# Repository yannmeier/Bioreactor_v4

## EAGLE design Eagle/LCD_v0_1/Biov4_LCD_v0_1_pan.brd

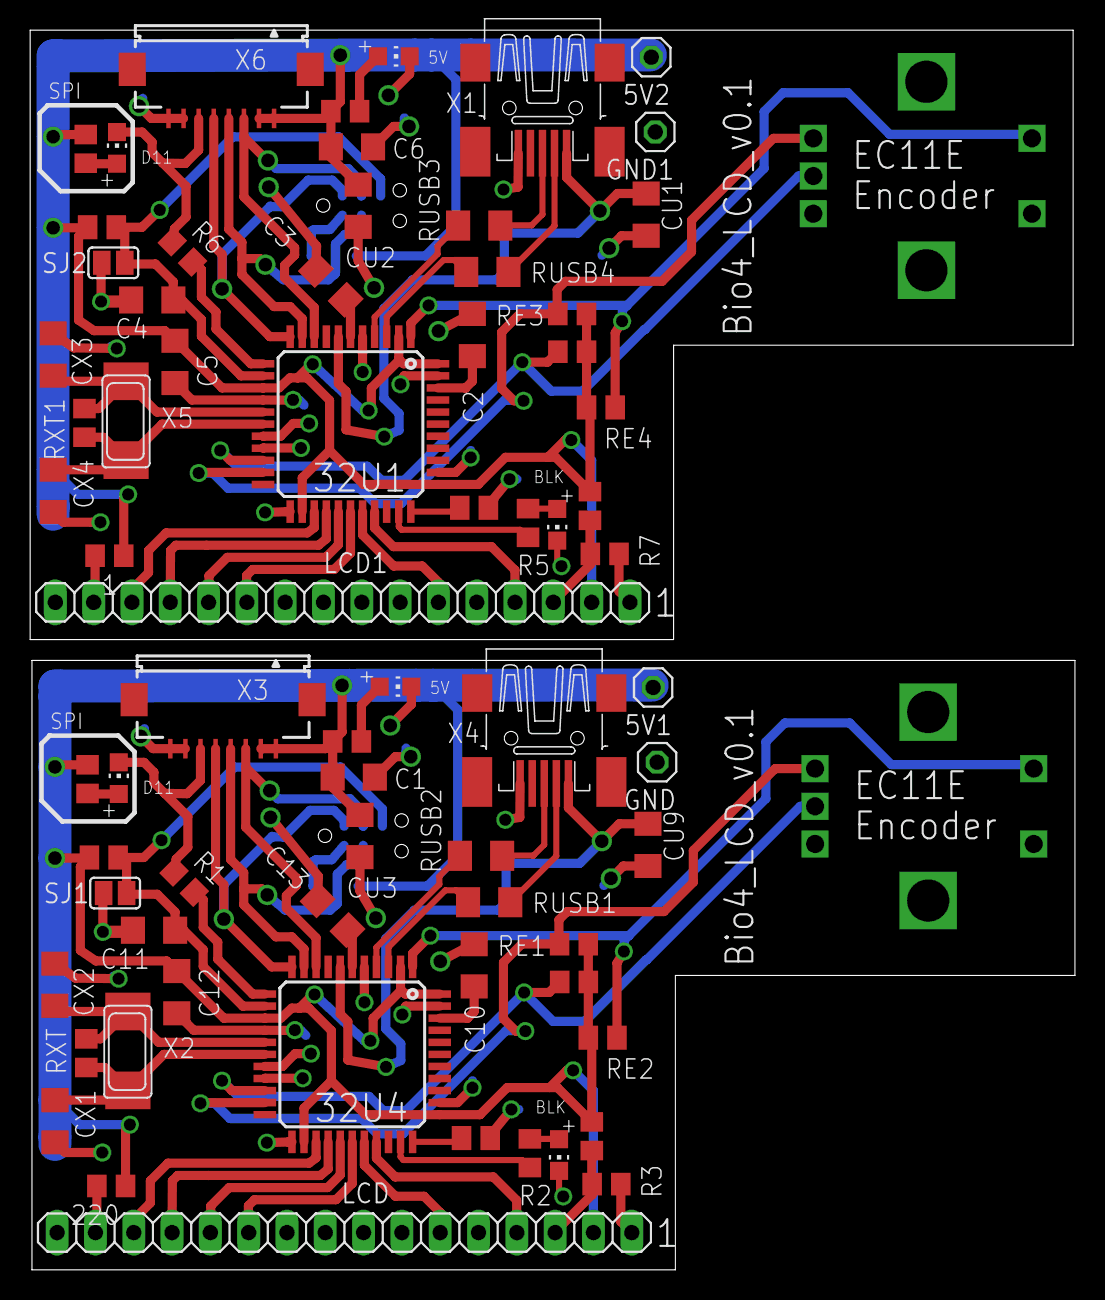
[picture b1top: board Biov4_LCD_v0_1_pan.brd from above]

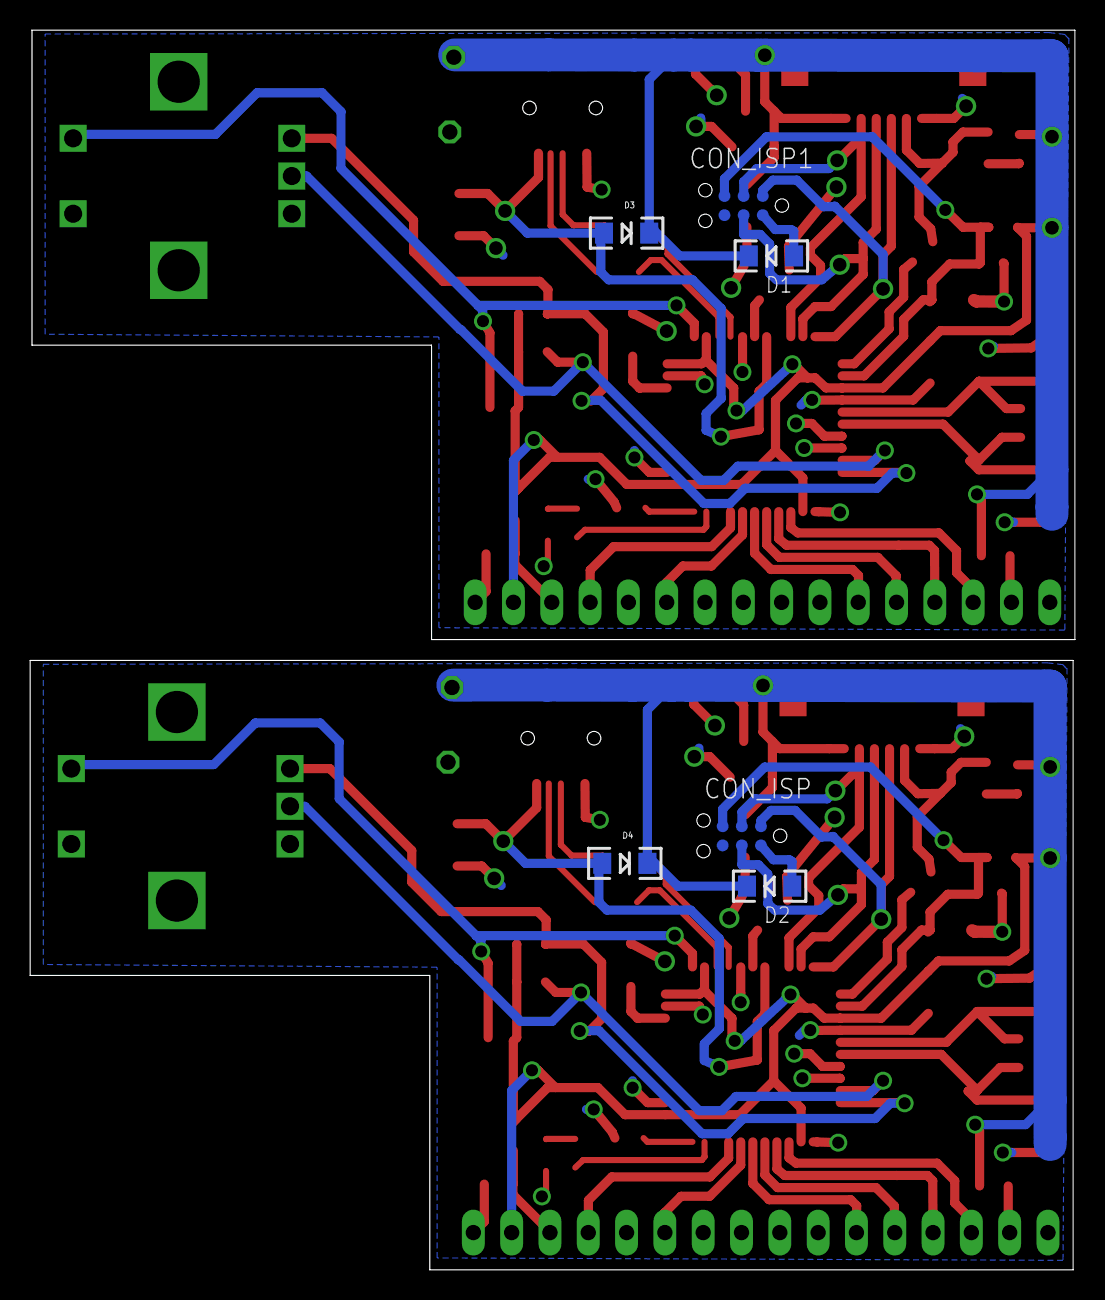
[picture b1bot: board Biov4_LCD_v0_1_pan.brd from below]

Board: 4 copper layers, 69.3 x 82.2 mm, 78 parts (6 on the bottom side), 68 nets.

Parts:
1, 220: 220; R0805
5V1, 5V2: 1X01
32U1, 32U4: ATMEGA32U4; TQFP44
BKLD, BKLD1: RED; CHIP-LED0805
C1, C2, C3, C4, C5, C6, C10, C11, C12, C13: 100nF; C1206
CON_ISP, CON_ISP1: SPI; TC2030-MCP-NL
CU1, CU2, CU3, CU9: 10uF; C1206
CX1, CX2, CX3, CX4: 22pF; C1206
D1, D2, D3, D4: 1N581D1206; LED-1206
GND, GND1: 1X01
LCD, LCD1: 1X16
LDPW1, LDPW5: RED; CHIP-LED0805
LDSLAVE, LDSLAVE1: RED; CHIP-LED0805
R1, R2, R3, R4, R5, R6, R7, R13: 1k; R0805
RE1, RE2, RE3, RE4: 5k; R0805
RK1, RK5, RK8, RK18: 10k; R0805
RK2, RK3, RK4, RK6, RK7, RK9: 10k; M0805
RUSB1, RUSB2, RUSB3, RUSB4: 22; M1206
RXT, RXT1: 1M; R0805
SJ1, SJ2: SJ
U$1, U$2: EC11E
X1, X4: MINI-USB; 32005-201
X2, X5: 16MHz; NX6035
X3, X6: FH12-08S-1SH

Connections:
+5V/1: 5V1.1, 32U4.2, 32U4.14, 32U4.24, 32U4.34, 32U4.44, 220.1, C1.1, C12.2, CU3.1, D2.C, D4.C, LCD.2, R13.1, RE1.1, RE2.1, RK1.1, RK2.2, RK6.2, RK18.1, X3.1, X3.2
+5V/2: 1.1, 5V2.1, 32U1.2, 32U1.14, 32U1.24, 32U1.34, 32U1.44, C5.2, C6.1, CU2.1, D1.C, D3.C, LCD1.2, R4.1, RE3.1, RE4.1, RK4.2, RK5.1, RK8.1, RK9.2, X6.1, X6.2
A6: 32U4.25, LCD.14
A13: 32U1.25, LCD1.14
AREF: 32U4.42, C10.1
AREF1: 32U1.42, C2.1
CS_32U1: LDSLAVE1.C, R6.1, X6.6
CS_32U4: LDSLAVE.C, R1.1, X3.6
D6*: 32U4.27, LCD.12
D6*1: 32U1.27, LCD1.12
D7*: 32U4.1, RK2.1, U$1.D
D7*1: 32U1.1, RK9.1, U$2.D
D8*: 32U4.28, LCD.11
D8*1: 32U1.28, LCD1.11
D9*: 32U4.29, LCD.6
D9*1: 32U1.29, LCD1.6
D10*: 32U4.30, LCD.4
D10*1: 32U1.30, LCD1.4
D11*: 32U4.12, R1.2
D11*1: 32U1.12, R6.2
D12*: 32U4.26, LCD.13
D12*1: 32U1.26, LCD1.13
D13*: 32U4.32, R2.1
D13*1: 32U1.32, R5.1
GND: 32U4.5, 32U4.15, 32U4.23, 32U4.35, 32U4.43, BKLD.C, C1.2, C10.2, C11.2, C12.1, C13.1, CON_ISP.GND, CU3.2, CU9.1, CX1.1, CX2.1, GND.1, LCD.1, LCD.5, LCD.16, LDPW5.C, R3.2, RK7.1, SJ1.1, U$1.C, U$1.E, X3.7, X3.8, X4.5
GND1: 32U1.5, 32U1.15, 32U1.23, 32U1.35, 32U1.43, BKLD1.C, C2.2, C3.1, C4.2, C5.1, C6.2, CON_ISP1.GND, CU1.1, CU2.2, CX3.1, CX4.1, GND1.1, LCD1.1, LCD1.5, LCD1.16, LDPW1.C, R7.2, RK3.1, SJ2.1, U$2.C, U$2.E, X1.5, X6.7, X6.8
HWB: 32U4.33, RK7.2
HWB1: 32U1.33, RK3.2
ISP+5V: CON_ISP.5V, D2.A
ISP+5V1: CON_ISP1.5V, D1.A
MISO: 32U4.11, CON_ISP.MISO, X3.5
MISO1: 32U1.11, CON_ISP1.MISO, X6.5
MOSI: 32U4.10, CON_ISP.MOSI, X3.4
MOSI1: 32U1.10, CON_ISP1.MOSI, X6.4
unnamed: 32U4.6, C13.2
unnamed: LCD.3, R3.1, RK1.2
unnamed: BKLD.A, R2.2
unnamed: LDPW1.A, R4.2
unnamed: BKLD1.A, R5.2
unnamed: 32U1.17, CX4.2, RXT1.2, X5.P$2
unnamed: 32U1.6, C3.2
unnamed: LDSLAVE1.A, RK5.2
unnamed: LCD1.3, R7.1, RK8.2
unnamed: 1.2, LCD1.15
unnamed: 220.2, LCD.15
unnamed: LDPW5.A, R13.2
unnamed: LDSLAVE.A, RK18.2
unnamed: 32U4.17, CX1.2, RXT.2, X2.P$2
RESET: 32U4.13, C11.1, CON_ISP.RESET, RK6.1, SJ1.2
RESET1: 32U1.13, C4.1, CON_ISP1.RESET, RK4.1, SJ2.2
RX: 32U4.20, RE2.2, U$1.B
RX1: 32U1.20, RE4.2, U$2.B
SCK: 32U4.9, CON_ISP.SCK, X3.3
SCK1: 32U1.9, CON_ISP1.SCK, X6.3
TX: 32U4.21, RE1.2, U$1.A
TX1: 32U1.21, RE3.2, U$2.A
USBC_N: RUSB1.2, X4.2
USBC_N1: RUSB4.2, X1.2
USBC_P: RUSB2.2, X4.3
USBC_P1: RUSB3.2, X1.3
USB_N: 32U4.3, RUSB1.1
USB_N1: 32U1.3, RUSB4.1
USB_P: 32U4.4, RUSB2.1
USB_P1: 32U1.4, RUSB3.1
VUSB: 32U4.7, CU9.2, D4.A, X4.1
VUSB1: 32U1.7, CU1.2, D3.A, X1.1
XTAL1: 32U4.16, CX2.2, RXT.1, X2.P$1
XTAL2: 32U1.16, CX3.2, RXT1.1, X5.P$1

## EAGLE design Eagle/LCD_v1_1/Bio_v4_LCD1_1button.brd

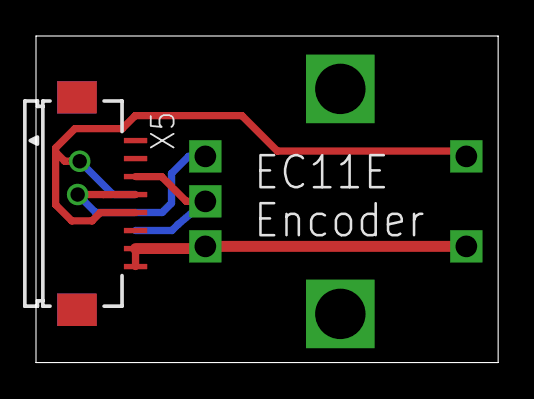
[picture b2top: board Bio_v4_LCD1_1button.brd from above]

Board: 4 copper layers, 25.7 x 18.1 mm, 3 parts (1 on the bottom side), 4 nets.

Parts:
U$1: EC11E
X5, X6: FH12-08S-1SH

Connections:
D7*: U$1.D, X5.5, X6.5
GND: U$1.C, U$1.E, X5.7, X5.8, X6.7, X6.8
RX: U$1.B, X5.3, X6.3
TX: U$1.A, X5.4, X6.4

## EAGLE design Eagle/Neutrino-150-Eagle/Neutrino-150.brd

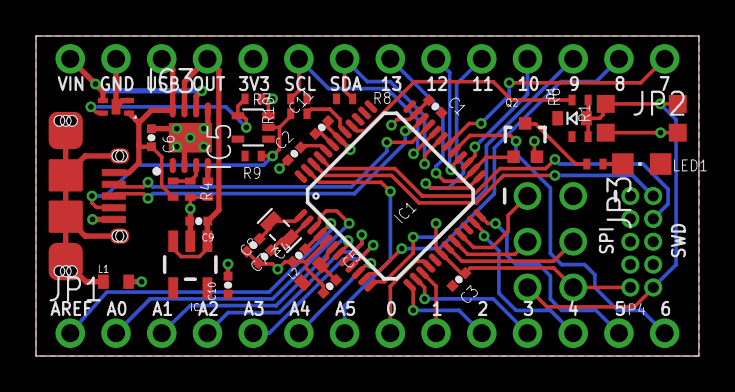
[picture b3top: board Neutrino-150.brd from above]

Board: 2 copper layers, 36.8 x 17.8 mm, 64 parts (0 on the bottom side), 49 nets.

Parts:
C1, C2, C3, C4, C5, C6: 100nF; 0402-CAP
C7, C8: 22pF; 0402-CAP
C9, C10, C11: 1uF; 0402-CAP
D1: SOD-523
IC1: SAMD21G18A-AUT; INTEGRATEDCIRCUITS_TQFP48-7X7
IC2: AP2112K-3.3; SOT23-5
IC3: TPS2115; 8-VDFN
IC4: SIP32401A; TDFN4
IC5: MC74VHC1G14DFT; SC70-5
JP1, JP2: 1X14_NO_SILK_SMALLPADS
JP3: SPI; CONNETTORI_2X03
JP4: SWD; CONNETTORI_PINHEAD-2X5-P127
L1, L2: 0603-TDK
LED1: Green; CHIPLED_0805
Q2: NFET; SOT323
R1, R3, R4, R9, R11: 100K; R0402-VISHAY
R2: 1K; R0402-VISHAY
R5, R6, R10: 330; R0402-VISHAY
R7, R8: 4.7K; R0402-VISHAY
SW1: KMR2
TP_0, TP_1, TP_2, TP_3, TP_3V3, TP_4, TP_5, TP_5V, TP_6, TP_7, TP_8, TP_9, TP_10, TP_12, TP_13: TP_SP; TP-SP
TP_A0, TP_A1, TP_A2, TP_A3, TP_A4, TP_A5: TP_SP; TP-SP
TP_AREF: TP_SP; TP-SP
TP_MOSI: TP_SP; TP-SP
TP_SCL: TP_SP; TP-SP
TP_SDA: TP_SP; TP-SP
USB: MICRO-AB; MOLEX_USB_MICRO_AB
Y1: 32,768Khz; CRYSTAL-SMD-2.0X1.2

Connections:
3.3V: C1.1, C2.1, C3.2, C10.1, D1.K, IC1.17, IC1.36, IC1.44, IC2.5, IC5.5, JP2.10, JP3.2, JP4.1, L2.1, LED1.A, R1.2, R7.2, R8.2, R9.2, TP_3V3.X
D1: IC3.3, R3.2, R4.2
DGI_GPIO1: IC1.30, JP2.1, TP_7.X
DGI_GPIO2: IC1.11, JP2.2, TP_8.X
DGI_GPIO3: IC1.12, JP2.3, TP_9.X
GND: C1.2, C2.2, C3.1, C4.2, C5.2, C6.2, C7.1, C8.1, C9.2, C10.2, C11.2, IC1.5, IC1.18, IC1.35, IC1.42, IC2.2, IC3.2, IC3.5, IC3.P0, IC3.V0, IC3.V1, IC3.V2, IC3.V3, IC3.V4, IC4.0, IC4.2, IC5.3, JP2.13, JP3.6, JP4.3, JP4.5, JP4.9, L1.2, Q2.2, R2.1, R4.1, R11.1, SW1.1, SW1.3, USB.P5
IC4_EN: IC4.4, IC5.4, R11.2
ILIM: IC3.4, R2.2
MISO: IC1.28, JP2.6, TP_12.X
MOSI: IC1.25, JP2.5, TP_MOSI.X
unnamed: LED1.C, R5.2
unnamed: Q2.3, R5.1
unnamed: IC5.2, R9.1, R10.1, USB.P4
PA00_XIN32: C7.2, IC1.1, Y1.2
PA01_XOUT32: C8.2, IC1.2, Y1.1
PA02_AIN0: IC1.3, JP1.2, TP_A0.X
PA03_AREFA: C4.1, IC1.4, JP1.1, TP_AREF.X
PA04_AIN4: IC1.9, JP1.5, TP_A3.X
PA05_AIN5: IC1.10, JP1.6, TP_A4.X
PA08_TCC0-W0: IC1.13, JP1.10, TP_2.X
PA09_TCC0-W1: IC1.14, JP1.11, TP_3.X
PA10_TCC0-W2: IC1.15, JP1.9, TP_1.X
PA11_TCC0-W3: IC1.16, JP1.8, TP_0.X
PA14_TCC0-W4: IC1.23, JP1.12, TP_4.X
PA15_TCC0-W5: IC1.24, JP1.13, TP_5.X
PA20_TCC0-W6: IC1.29, JP1.14, TP_6.X
PA28_USB_HOST_EN: IC1.41, R10.2
PA30_SWCLK: IC1.45, JP4.4
PA31_SWDIO: IC1.46, JP4.2
PB02_AIN10: IC1.47, JP1.7, TP_A5.X
PB08_AIN2: IC1.7, JP1.3, TP_A1.X
PB09_AIN3: IC1.8, JP1.4, TP_A2.X
PB10_S4_SPI_MOSI: IC1.19, JP3.4
PB11_S4_SPI_SCK: IC1.20, JP3.3
PB12_S4_SPI_MISO: IC1.21, JP3.1
RESET: D1.A, JP3.5, JP4.10, R1.1, R6.2, SW1.2, SW1.4
SCK: IC1.26, JP2.7, Q2.1, TP_13.X
SCL: IC1.32, JP2.9, R7.1, TP_SCL.X
SDA: IC1.31, JP2.8, R8.1, TP_SDA.X
SHIELD: L1.1, USB.S1, USB.S2, USB.S3, USB.S4, USB.S5, USB.S6
SS: IC1.27, JP2.4, TP_10.X
TARGET_RESET_EDBG: IC1.40, R6.1
TARGET_USB_N: IC1.33, USB.P2
TARGET_USB_P: IC1.34, USB.P3
VBUS: C6.1, IC3.8, IC4.1, JP2.12, R3.1, USB.P1
VDDANA: C5.1, IC1.6, L2.2
VDDCORE: C11.1, IC1.43
VIN: IC3.6, IC4.3, JP2.14
VOUT: C9.1, IC2.1, IC2.3, IC3.7, JP2.11

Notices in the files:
parts and their libraries:
lpatiny: ©2009 ROFA.cz - modified and updated by Robert Darlington ‹rdarlington@gmail.com›
SparkFun-Connectors: Licensing: Creative Commons ShareAlike 4.0 International - https://creativecommons.org/licenses/by-sa/4.0
